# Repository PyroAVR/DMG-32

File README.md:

Emulator Project
================
I don't have a witty name for this...  This repository contains all the things necessary for making a working Retroarch emulator that fits inside a DMG GameBoy, -or- later, a custom casing with added awesomeness.
Below are the projects which have been used to build this one...

###What changed?
Here's a list of the changes made to the original Adafruit code.
 -Added a new I/O type.  Support for the Pixel interface board.
 -10-retrogame.rules added.  Just copy it into the `/etc/udev/rules.d/` folder!
 -Added retrogame.sh, it's a really handy sysV start script for retrogame!
 -TODO: recompile new retrogame with Pixel interface board support.
Adafruit-Retrogame
==================

Raspberry Pi GPIO-to-USB utility for classic game emulators.

How-to: http://learn.adafruit.com/retro-gaming-with-raspberry-pi

Pre-built version supports the default pin/key mapping shown in the tutorial. For other layouts, edit retrogame.c.

### RetroPie 2.0+ Compatibility

Note that by default retrogame won't work with SDL2 applications that depend on evdev for input events.  Specifically this means applications like the latest version of RetroPie and EmulationStation won't be able to see key events generated by retrogame.  However you can fix this issue by adding a small custom udev rule to make retrogame keyboard events visible to SDL2.

Connect to your Raspberry Pi in a terminal/SSH session and execute the following command to create and edit the file /etc/udev/rules.d/10-retrogame.rules:

```bash
sudo nano /etc/udev/rules.d/10-retrogame.rules
```

Once the nano text editor loads, copy this single line into the file:

```bash
SUBSYSTEM=="input", ATTRS{name}=="retrogame", ENV{ID_INPUT_KEYBOARD}="1"
```

Save the file by pressing Ctrl-O and enter, then press Ctrl-x to exit.  Restart your Raspberry Pi and run retrogame again, now button presses should register in SDL2 applications like the EmulationStation frontend to RetroPie

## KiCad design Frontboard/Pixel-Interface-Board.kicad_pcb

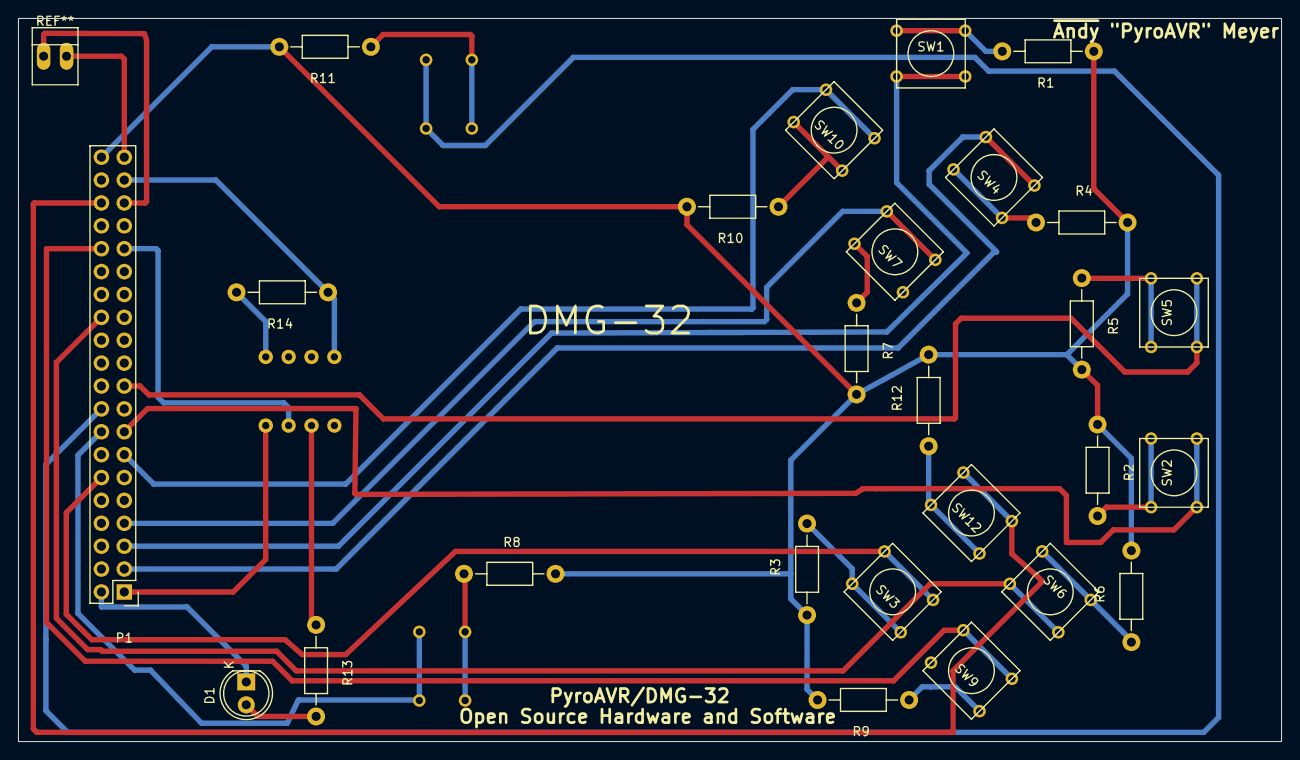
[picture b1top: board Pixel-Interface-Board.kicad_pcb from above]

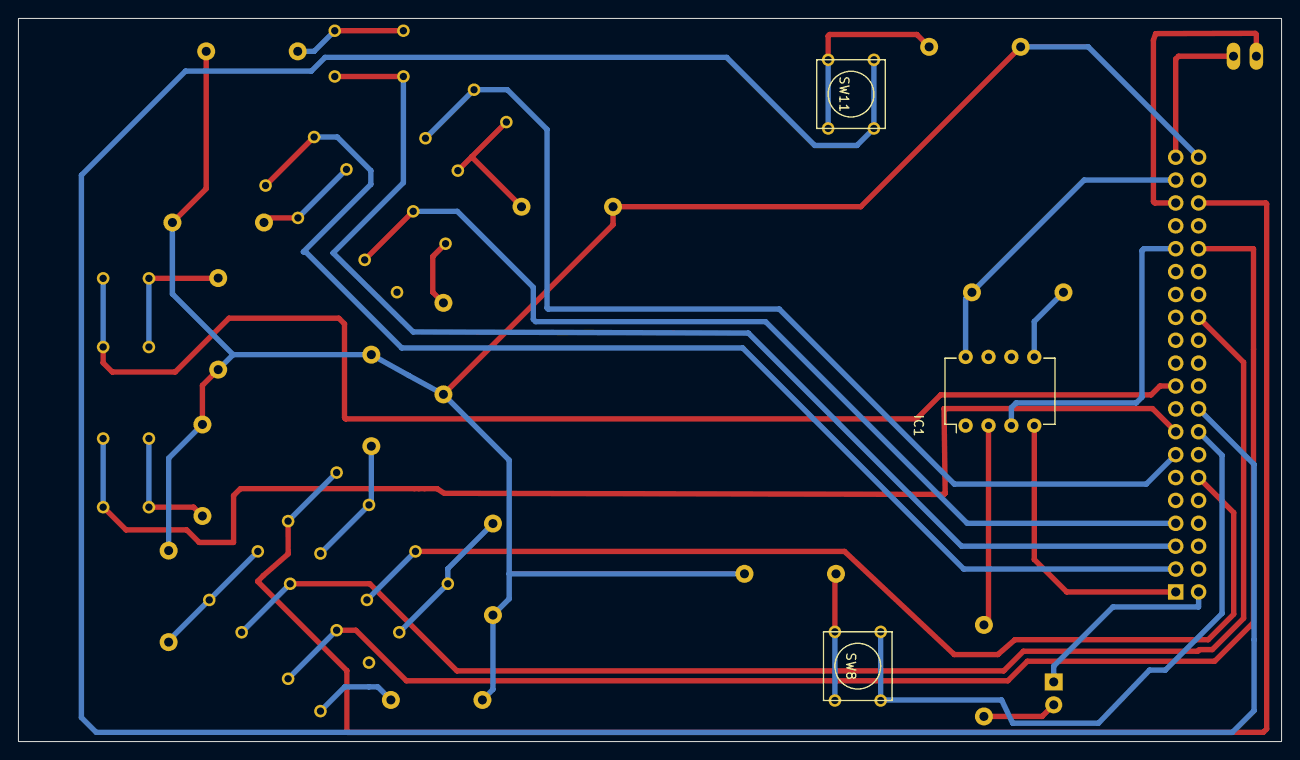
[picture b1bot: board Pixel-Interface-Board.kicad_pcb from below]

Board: 2 copper layers, 140.2 x 80.3 mm, 29 parts (3 on the bottom side), 31 nets.

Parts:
D1: LED; LED-5MM
IC1: ATTINY85-P; DIP-8_W7.62mm
P1: CONN_02X20; Pin_Header_Straight_2x20
R1, R2, R3, R4, R5, R6, R7, R8, R9, R10, R11, R12, R14: 10K; Resistor_Horizontal_RM10mm
R13: 1K; Resistor_Horizontal_RM10mm
SW1, SW2, SW3, SW4, SW5, SW6, SW7, SW8, SW9, SW10, SW11, SW12: SW_PUSH; SW_PUSH_SMALL

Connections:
/A: P1.5, SW1.2
/B: P1.3, SW4.2
/DOWN: P1.26, SW6.2
/L: P1.16, SW8.2
/LEFT: P1.32, SW9.2
/R: P1.18, SW11.2
/RIGHT: P1.36, SW12.2
/SELECT: P1.15, SW2.2
/START: P1.19, SW5.2
/UART_RX: IC1.3, P1.31
/UP: P1.12, SW3.2
/X: P1.7, SW7.2
/Y: P1.13, SW10.2
GND: D1.1, IC1.4, P1.1, P1.2, P1.9, P1.21, P1.30, P1.34, P1.35
unnamed: D1.2, R13.2
unnamed: IC1.2, R13.1
unnamed: IC1.5, R14.2
unnamed: R1.2, SW1.1
unnamed: R2.2, SW2.1
unnamed: R3.2, SW3.1
unnamed: R4.1, SW4.1
unnamed: R5.1, SW5.1
unnamed: R6.1, SW6.1
unnamed: R7.1, SW7.1
unnamed: R8.1, SW8.1
unnamed: R9.1, SW9.1
unnamed: R10.1, SW10.1
unnamed: R11.1, SW11.1
unnamed: R12.1, SW12.1
VCC: IC1.8, P1.37, P1.39, R14.1
VDD: P1.24, P1.40, R1.1, R2.1, R3.1, R4.2, R5.2, R6.2, R7.2, R8.2, R9.2, R10.2, R11.2, R12.2

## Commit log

2015-05-25 Added init script
2015-05-25 make install adds initscript
2015-07-27 Added initial PCB stuff. Probably doesn't work.
2015-08-19 Almost done with the Front Board!
2015-09-23 Probably update the board and stuff...
2015-09-24 px_retrogame customizations complete??
2015-11-12 Fixed the interface board, FINALLY.
2016-01-24 Fixed R trace to fit within OSHPark specs. Unfortunately, a very long trace circling the entire board has resulted from this.
2016-01-24 Added board outline to the proper layer.
2016-01-24 Oooh, silkscreen...
2016-01-27 Directories moved, .gitignore added. Major changes to Frontboard design. Header was completely backwards, fixed now, pins re-arranged. Table coming shortly.
2016-01-27 Added table to show hardware->software connections.
2016-01-27 Tentative fixes for ioPixel, as well as removing potential confusion due to board auto-detection, which is thankfully not necessary.
2016-01-27 Fixed makefile and sysV script for startup. Type make pixel-install !
2016-01-27 Working on start script, turns out it doesn't actually work as intended.
2016-01-27 Removed stray files
2016-01-27 start-stop-daemon may fix this?
2016-01-27 more start-stop-daemon
2016-01-27 Maybe this will work\!
2016-01-27 Fixed! Finally!
2016-01-30 removing vulcanMask
    removed vulcanMask assignment so escape is never sent. Very likely to be causing crashes in testing where not all pins are connected.
2016-01-31 Fixed Gcode, hopefully. Z-depth for isolation lowered, Z-depth for drill increased.
2016-01-31 Switched vulcanKey to Q to remove confusion. Will configure retroarch to use Q to raise menu overlays and include retroarch.cfg
2016-01-31 Splashscreen graphic
2016-01-31 Retroarch config for DMG-32. Hopefully final.
2016-02-06 Minor edits to circuitboard front which may help eliminate issues with CAM processing.
2016-02-06 Fixed Gerber, re-exported. Alignment and spacing looking good. Gcode added into repo again, generated by FlatCAM.
2016-02-06 Shifted Gcode up by 96 mm to center lower-left corner near (0,0). Shift applied by PyroAVR/Gcode-Manipulator
2016-02-06 Fixed cutout to take many passes.
2016-02-12 Added power port to pcb, rpi micro usb power port no longer used. Exported new Gerber and Gcode.
2016-02-13 Started working on BOM
2017-01-11 changes made for use w/ Kitsch-Bent PCB.
2017-01-11 updated docs/using pi0
2017-01-11 gpio alteration program/service file added
2017-01-11 Re-enabled pull-up resistor setter for safety.
2017-01-13 recompiled retrogame
2017-01-13 Rebuild
2017-01-13 Moved pin due to pullup on BCM7 bot working. 7->5
2017-01-13 rebuilt retrogame - this is a bad way to transfer files
2017-01-15 Sync from USB to provide updates.
